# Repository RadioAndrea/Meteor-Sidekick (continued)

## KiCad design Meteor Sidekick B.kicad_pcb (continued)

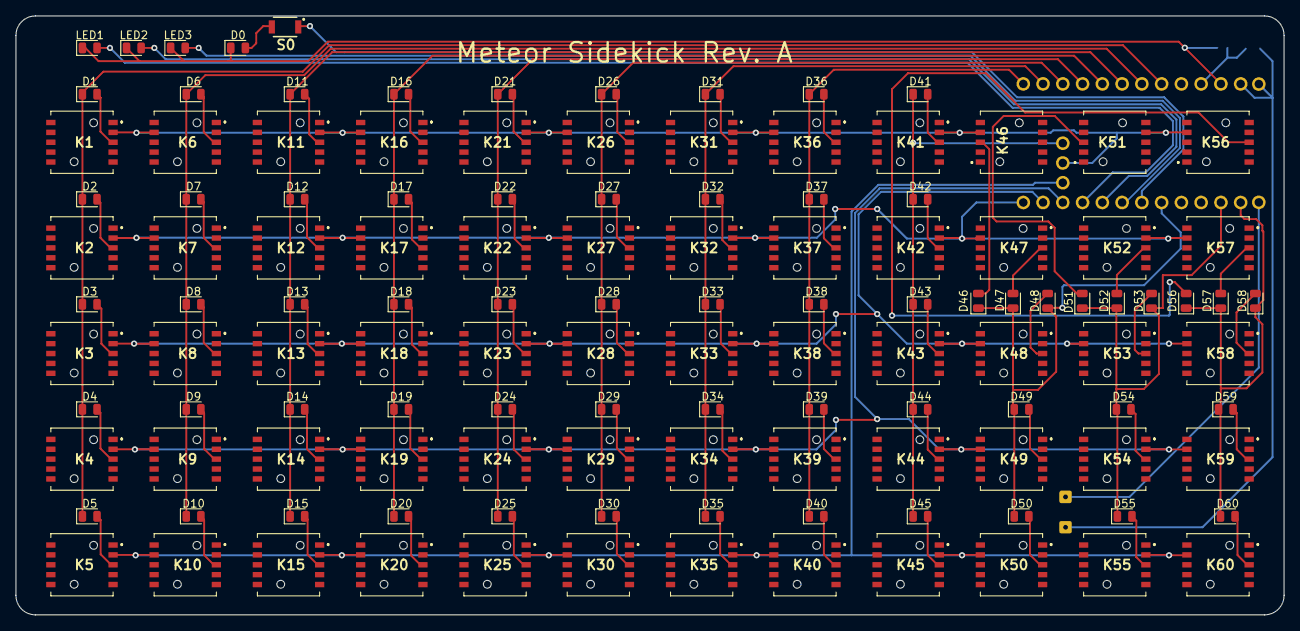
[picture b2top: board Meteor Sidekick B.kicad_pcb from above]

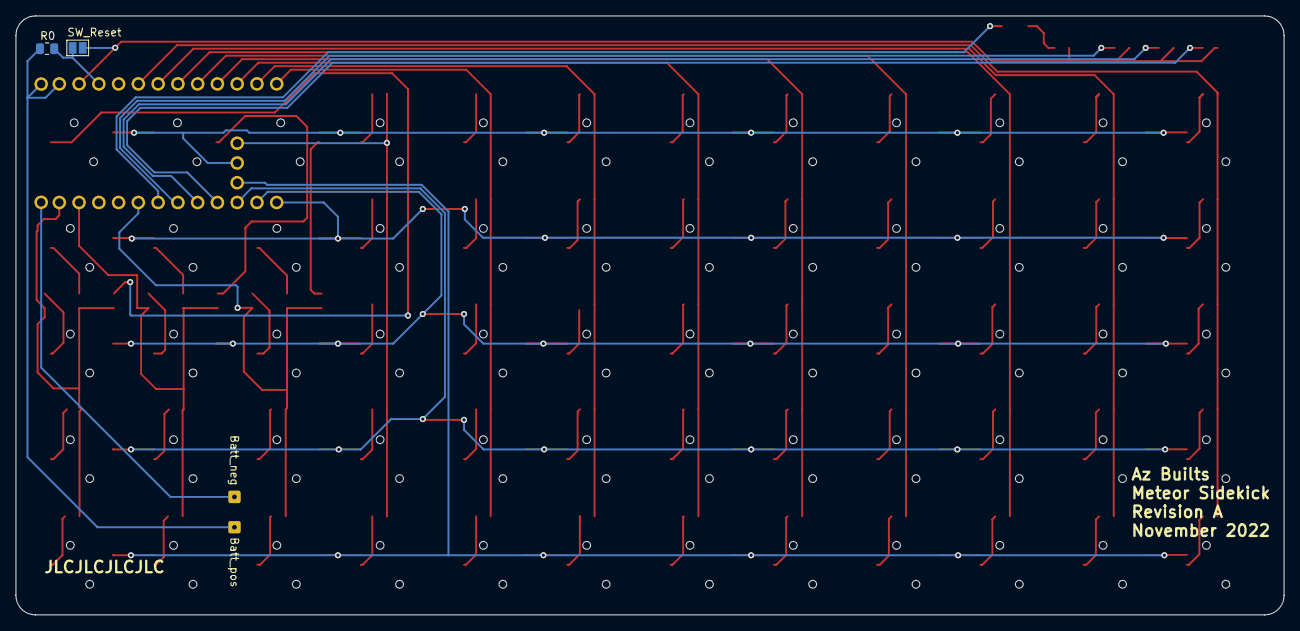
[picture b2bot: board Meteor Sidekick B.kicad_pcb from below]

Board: 2 copper layers, 163.0 x 77.0 mm, 130 parts (5 on the bottom side), 85 nets.

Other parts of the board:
SW_Reset: SW_Reset; SolderJumper-2_P1.3mm_Open_Pad1.0x1.5mm

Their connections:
GND: SW_Reset.1; also elsewhere on the board
unnamed 84: SW_Reset.2; also elsewhere on the board

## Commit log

2022-11-07 Initial Commit
    Adds Rev A board
2022-11-10 Rev B initial - ground plane
    Added ground plane to both sides of the board
2022-11-24 Added initial kailh designs
    Added a design for kailh chocos and x scissors
2022-11-24 Fixed reset and batt on isolated gnd
2022-12-10 Fixed missed connections
    Reset now connected
    LEDs now connected
2022-12-10 Created board cut files
2023-07-31 Adding graphics to enhance engagement
2023-07-31 replace wrong front render
2023-07-31 re-replace front render
2024-01-09 Adding photos of progress
2024-01-09 Fix image link
